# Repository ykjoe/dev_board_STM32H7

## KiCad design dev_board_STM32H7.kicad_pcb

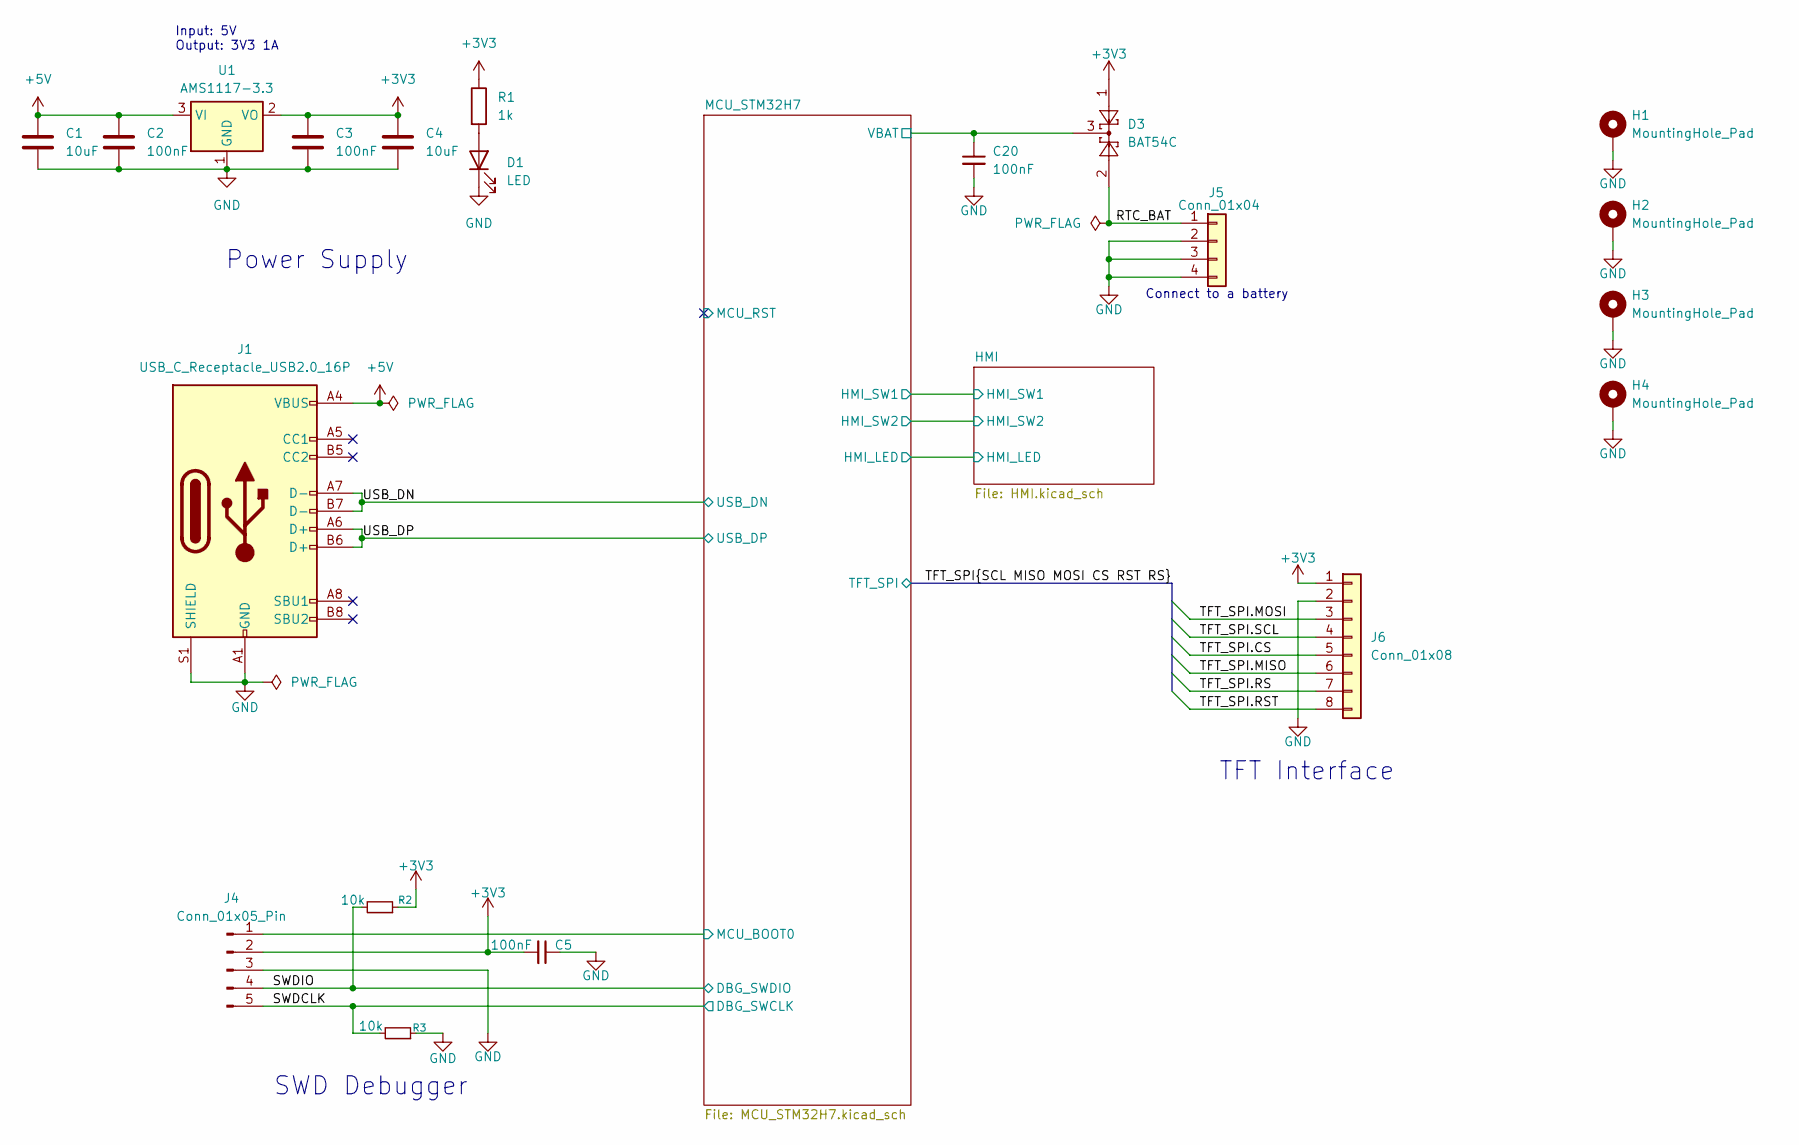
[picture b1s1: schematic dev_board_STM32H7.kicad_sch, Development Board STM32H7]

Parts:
C1, C4: 10uF; C_0805_2012Metric
C2, C3, C5, C20: 100nF; C_0402_1005Metric
D1: LED; LED_0603_1608Metric
D3: BAT54C; SOT-23
H1, H2, H3, H4: MountingHole_Pad; MountingHole_3mm_Pad
J1: USB_C_Receptacle_USB2.0_16P; USB-C-SMD_TYPE-C-16P-1
J4: Conn_01x05_Pin; PinHeader_1x05_P2.54mm_Vertical
J5: Conn_01x04; CONN-SMD_532610271
J6: Conn_01x08; PinHeader_1x08_P2.54mm_Vertical
R1: 1k; R_0402_1005Metric
R2, R3: 10k; R_0402_1005Metric
U1: AMS1117-3.3; SOT-223-3_TabPin2

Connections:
+3V3: C3.1, C4.1, C5.2, D3.1, J4.2, J6.1, R1.1, R2.1, U1.2 (VO); also elsewhere on the board
+5V: C1.1, C2.1, J1.A4 (VBUS), J1.A9 (VBUS), J1.B4 (VBUS), J1.B9 (VBUS), U1.3 (VI); also elsewhere on the board
/MCU_STM32H7/MCU_BOOT0: J4.1; also elsewhere on the board
/MCU_STM32H7/VBAT: C20.1, D3.3; also elsewhere on the board
/RTC_BAT: D3.2, J5.1
/SWDCLK: J4.5, R3.2; also elsewhere on the board
/SWDIO: J4.4, R2.2; also elsewhere on the board
/TFT_SPI.CS: J6.5; also elsewhere on the board
/TFT_SPI.MISO: J6.6; also elsewhere on the board
/TFT_SPI.MOSI: J6.3; also elsewhere on the board
/TFT_SPI.RS: J6.7; also elsewhere on the board
/TFT_SPI.RST: J6.8; also elsewhere on the board
/TFT_SPI.SCL: J6.4; also elsewhere on the board
/USB_DN: J1.A7 (D-), J1.B7 (D-); also elsewhere on the board
/USB_DP: J1.A6 (D+), J1.B6 (D+); also elsewhere on the board
GND: C1.2, C2.2, C3.2, C4.2, C5.1, C20.2, D1.1 (K), H1.1, H2.1, H3.1, H4.1, J1.A1 (GND), J1.A12 (GND), J1.B1 (GND), J1.B12 (GND), J1.S1 (SHIELD), J4.3, J5.2, J5.3, J5.4, J6.2, R3.1, U1.1 (GND); also elsewhere on the board
unnamed: D1.2 (A), R1.2

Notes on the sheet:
SWD Debugger
Connect to a battery
Power Supply
TFT Interface
Input: 5V Output: 3V3 1A

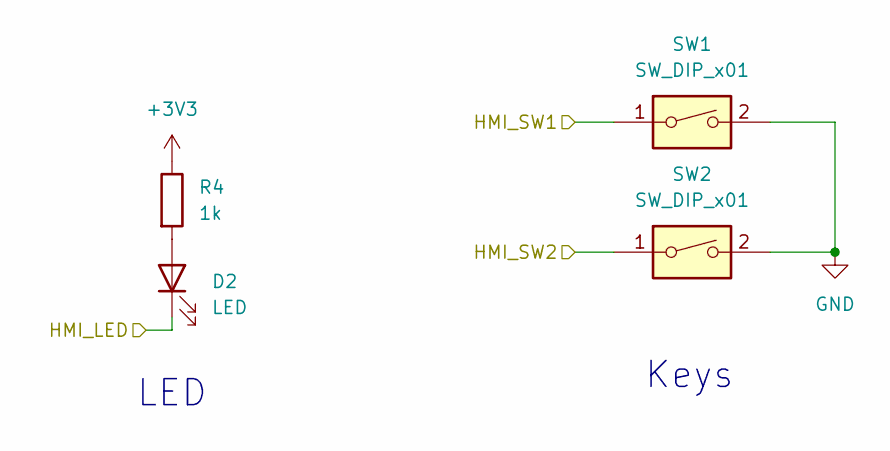
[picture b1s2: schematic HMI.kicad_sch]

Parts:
D2: LED; LED_0603_1608Metric
R4: 1k; R_0402_1005Metric
SW1, SW2: SW_DIP_x01; SW_DIP_SPSTx01_Slide_Copal_CHS-01A_W5.08mm_P1.27mm_JPin

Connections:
+3V3: R4.1; also elsewhere on the board
/MCU_STM32H7/PA1: D2.1 (K); also elsewhere on the board
/MCU_STM32H7/PC5: SW2.1; also elsewhere on the board
/MCU_STM32H7/PE3: SW1.1; also elsewhere on the board
GND: SW1.2, SW2.2; also elsewhere on the board
unnamed: D2.2 (A), R4.2

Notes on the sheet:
Keys
LED

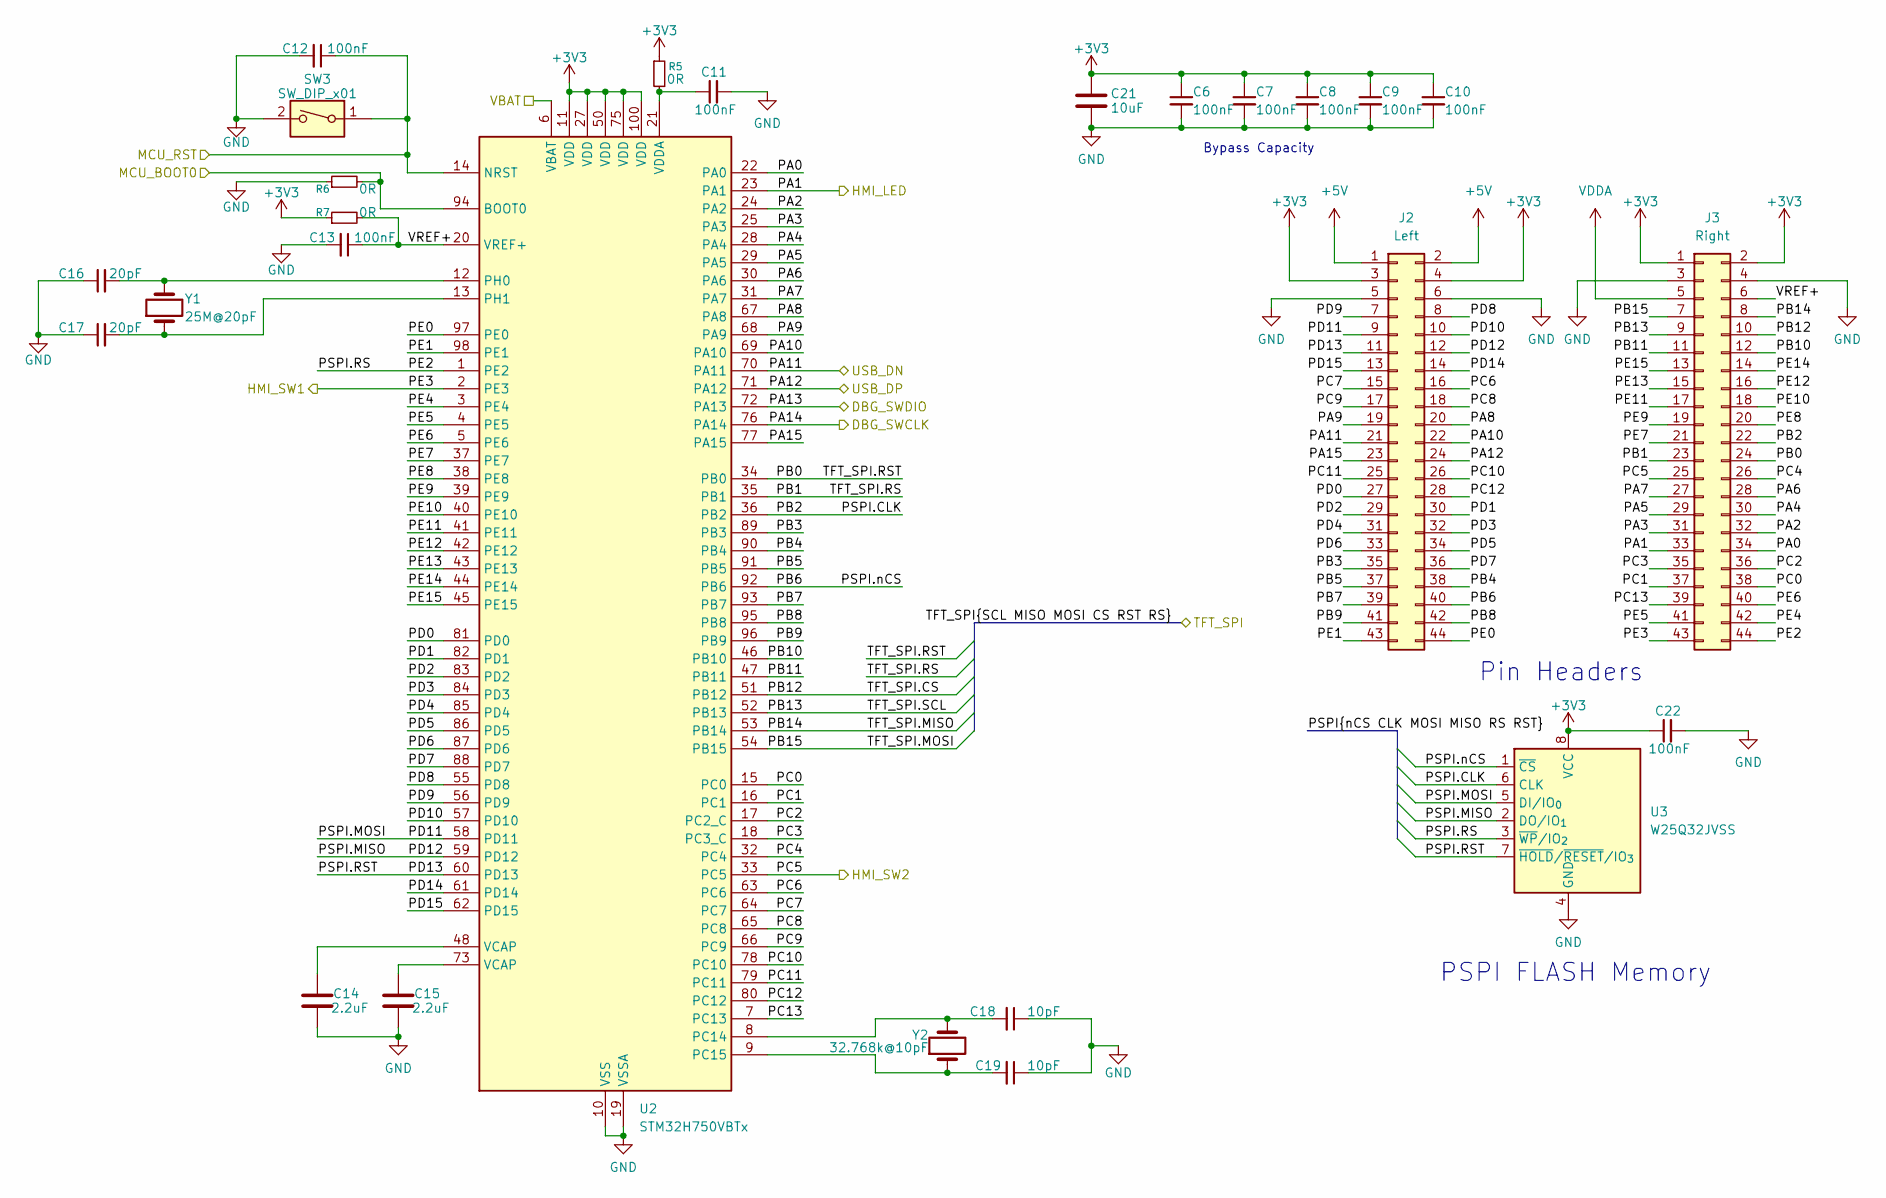
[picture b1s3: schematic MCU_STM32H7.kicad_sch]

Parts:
C6, C7, C8, C9, C10, C11, C12, C13, C22: 100nF; C_0402_1005Metric
C14, C15: 2.2uF; C_0603_1608Metric
C16, C17: 20pF; C_0402_1005Metric
C18, C19: 10pF; C_0402_1005Metric
C21: 10uF; C_0805_2012Metric
J2: Left; PinHeader_2x22_P2.54mm_Vertical
J3: Right; PinHeader_2x22_P2.54mm_Vertical
R5, R6, R7: 0R; R_0402_1005Metric
SW3: SW_DIP_x01; SW_DIP_SPSTx01_Slide_Copal_CHS-01A_W5.08mm_P1.27mm_JPin
U2: STM32H750VBTx; LQFP-100_14x14mm_P0.5mm
U3: W25Q32JVSS; SOIC-8_5.3x5.3mm_P1.27mm
Y1: 25M@20pF; Crystal_SMD_5032-2Pin_5.0x3.2mm
Y2: 32.768k@10pF; Crystal_SMD_3215-2Pin_3.2x1.5mm

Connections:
+3V3: C6.1, C7.1, C8.1, C9.1, C10.1, C21.1, C22.1, J2.3, J2.4, J3.1, J3.2, R5.1, R7.1, U2.11 (VDD), U2.27 (VDD), U2.50 (VDD), U2.75 (VDD), U2.100 (VDD), U3.8 (VCC); also elsewhere on the board
+5V: J2.1, J2.2; also elsewhere on the board
/MCU_STM32H7/MCU_BOOT0: R6.2, U2.94 (BOOT0); also elsewhere on the board
/MCU_STM32H7/MCU_RST: C12.1, SW3.1, U2.14 (NRST)
/MCU_STM32H7/PA0: J3.34, U2.22 (PA0)
/MCU_STM32H7/PA1: J3.33, U2.23 (PA1); also elsewhere on the board
/MCU_STM32H7/PA2: J3.32, U2.24 (PA2)
/MCU_STM32H7/PA3: J3.31, U2.25 (PA3)
/MCU_STM32H7/PA4: J3.30, U2.28 (PA4)
/MCU_STM32H7/PA5: J3.29, U2.29 (PA5)
/MCU_STM32H7/PA6: J3.28, U2.30 (PA6)
/MCU_STM32H7/PA7: J3.27, U2.31 (PA7)
/MCU_STM32H7/PA8: J2.20, U2.67 (PA8)
/MCU_STM32H7/PA9: J2.19, U2.68 (PA9)
/MCU_STM32H7/PA10: J2.22, U2.69 (PA10)
/MCU_STM32H7/PA15: J2.23, U2.77 (PA15)
/MCU_STM32H7/PB3: J2.35, U2.89 (PB3)
/MCU_STM32H7/PB4: J2.38, U2.90 (PB4)
/MCU_STM32H7/PB5: J2.37, U2.91 (PB5)
/MCU_STM32H7/PB7: J2.39, U2.93 (PB7)
/MCU_STM32H7/PB8: J2.42, U2.95 (PB8)
/MCU_STM32H7/PB9: J2.41, U2.96 (PB9)
/MCU_STM32H7/PB10: J3.12, U2.46 (PB10)
/MCU_STM32H7/PB11: J3.11, U2.47 (PB11)
/MCU_STM32H7/PC0: J3.38, U2.15 (PC0)
/MCU_STM32H7/PC1: J3.37, U2.16 (PC1)
/MCU_STM32H7/PC2: J3.36, U2.17 (PC2_C)
/MCU_STM32H7/PC3: J3.35, U2.18 (PC3_C)
/MCU_STM32H7/PC4: J3.26, U2.32 (PC4)
/MCU_STM32H7/PC5: J3.25, U2.33 (PC5); also elsewhere on the board
/MCU_STM32H7/PC6: J2.16, U2.63 (PC6)
/MCU_STM32H7/PC7: J2.15, U2.64 (PC7)
/MCU_STM32H7/PC8: J2.18, U2.65 (PC8)
/MCU_STM32H7/PC9: J2.17, U2.66 (PC9)
/MCU_STM32H7/PC10: J2.26, U2.78 (PC10)
/MCU_STM32H7/PC11: J2.25, U2.79 (PC11)
/MCU_STM32H7/PC12: J2.28, U2.80 (PC12)
/MCU_STM32H7/PC13: J3.39, U2.7 (PC13)
/MCU_STM32H7/PD0: J2.27, U2.81 (PD0)
/MCU_STM32H7/PD1: J2.30, U2.82 (PD1)
/MCU_STM32H7/PD2: J2.29, U2.83 (PD2)
/MCU_STM32H7/PD3: J2.32, U2.84 (PD3)
/MCU_STM32H7/PD4: J2.31, U2.85 (PD4)
/MCU_STM32H7/PD5: J2.34, U2.86 (PD5)
/MCU_STM32H7/PD6: J2.33, U2.87 (PD6)
/MCU_STM32H7/PD7: J2.36, U2.88 (PD7)
/MCU_STM32H7/PD8: J2.8, U2.55 (PD8)
/MCU_STM32H7/PD9: J2.7, U2.56 (PD9)
/MCU_STM32H7/PD10: J2.10, U2.57 (PD10)
/MCU_STM32H7/PD14: J2.14, U2.61 (PD14)
/MCU_STM32H7/PD15: J2.13, U2.62 (PD15)
/MCU_STM32H7/PE0: J2.44, U2.97 (PE0)
/MCU_STM32H7/PE1: J2.43, U2.98 (PE1)
/MCU_STM32H7/PE3: J3.43, U2.2 (PE3); also elsewhere on the board
/MCU_STM32H7/PE4: J3.42, U2.3 (PE4)
/MCU_STM32H7/PE5: J3.41, U2.4 (PE5)
/MCU_STM32H7/PE6: J3.40, U2.5 (PE6)
/MCU_STM32H7/PE7: J3.21, U2.37 (PE7)
/MCU_STM32H7/PE8: J3.20, U2.38 (PE8)
/MCU_STM32H7/PE9: J3.19, U2.39 (PE9)
/MCU_STM32H7/PE10: J3.18, U2.40 (PE10)
/MCU_STM32H7/PE11: J3.17, U2.41 (PE11)
/MCU_STM32H7/PE12: J3.16, U2.42 (PE12)
/MCU_STM32H7/PE13: J3.15, U2.43 (PE13)
/MCU_STM32H7/PE14: J3.14, U2.44 (PE14)
/MCU_STM32H7/PE15: J3.13, U2.45 (PE15)
/MCU_STM32H7/PSPI.CLK: J3.22, U2.36 (PB2), U3.6 (CLK)
/MCU_STM32H7/PSPI.MISO: J2.12, U2.59 (PD12), U3.2 (DO/IO_{1})
/MCU_STM32H7/PSPI.MOSI: J2.9, U2.58 (PD11), U3.5 (DI/IO_{0})
/MCU_STM32H7/PSPI.RS: J3.44, U2.1 (PE2), U3.3 (~WP/IO_{2})
/MCU_STM32H7/PSPI.RST: J2.11, U2.60 (PD13), U3.7 (~HOLD/~RESET/IO_{3})
/MCU_STM32H7/PSPI.nCS: J2.40, U2.92 (PB6), U3.1 (~CS)
/MCU_STM32H7/VBAT: U2.6 (VBAT); also elsewhere on the board
/MCU_STM32H7/VREF+: C13.1, J3.6, R7.2, U2.20 (VREF+)
/SWDCLK: U2.76 (PA14); also elsewhere on the board
/SWDIO: U2.72 (PA13); also elsewhere on the board
/TFT_SPI.CS: J3.10, U2.51 (PB12); also elsewhere on the board
/TFT_SPI.MISO: J3.8, U2.53 (PB14); also elsewhere on the board
/TFT_SPI.MOSI: J3.7, U2.54 (PB15); also elsewhere on the board
/TFT_SPI.RS: J3.23, U2.35 (PB1); also elsewhere on the board
/TFT_SPI.RST: J3.24, U2.34 (PB0); also elsewhere on the board
/TFT_SPI.SCL: J3.9, U2.52 (PB13); also elsewhere on the board
/USB_DN: J2.21, U2.70 (PA11); also elsewhere on the board
/USB_DP: J2.24, U2.71 (PA12); also elsewhere on the board
GND: C6.2, C7.2, C8.2, C9.2, C10.2, C11.2, C12.2, C13.2, C14.1, C15.1, C16.1, C17.1, C18.1, C19.1, C21.2, C22.2, J2.5, J2.6, J3.3, J3.4, R6.1, SW3.2, U2.10 (VSS), U2.19 (VSSA), U2.26 (VSS), U2.49 (VSS), U2.74 (VSS), U2.99 (VSS), U3.4 (GND); also elsewhere on the board
unnamed: C14.2, U2.48 (VCAP)
unnamed: C15.2, U2.73 (VCAP)
unnamed: C18.2, U2.8 (PC14), Y2.2
unnamed: C19.2, U2.9 (PC15), Y2.1
unnamed: C16.2, U2.12 (PH0), Y1.2
unnamed: C17.2, U2.13 (PH1), Y1.1
unnamed: C11.1, R5.2, U2.21 (VDDA)
VDDA: J3.5

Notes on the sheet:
Bypass Capacity
PSPI FLASH Memory
Pin Headers

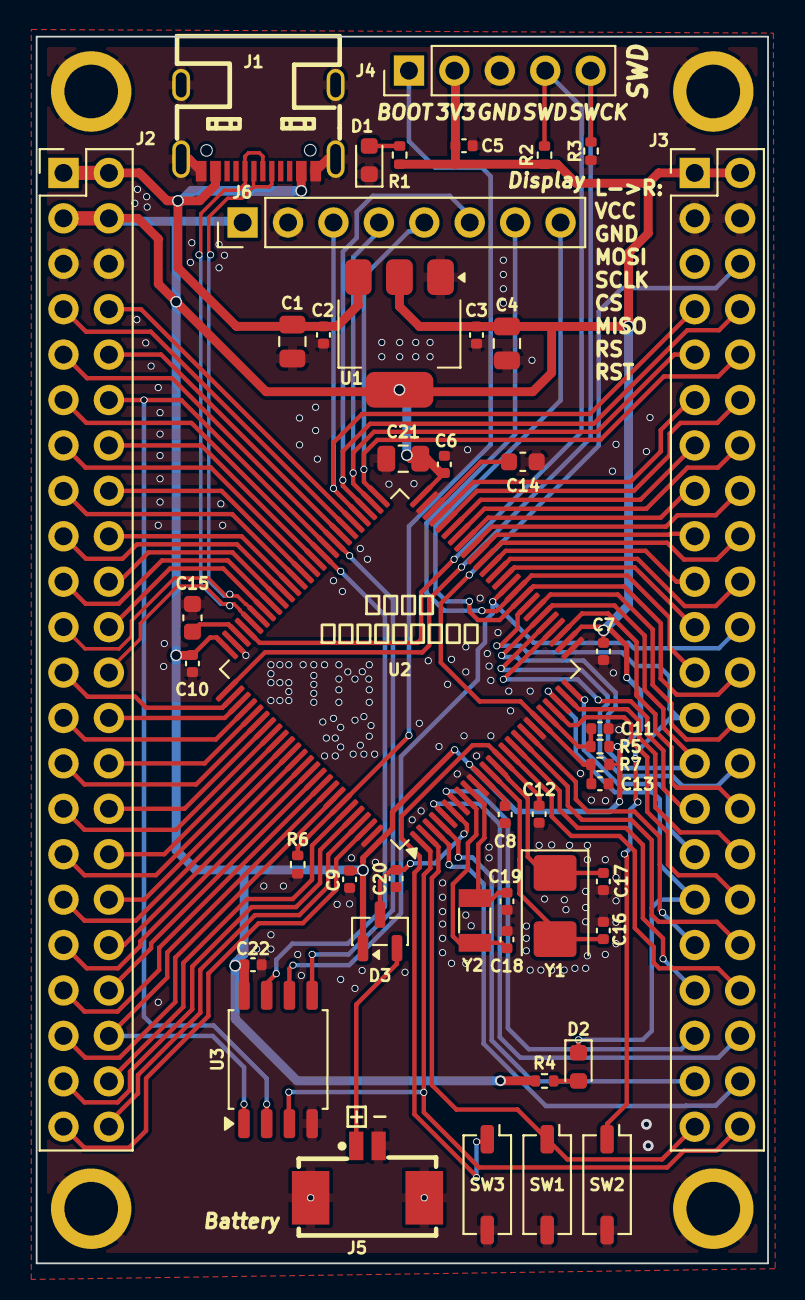
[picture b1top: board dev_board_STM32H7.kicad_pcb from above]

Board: 2 copper layers, 40.9 x 68.6 mm, 50 parts (0 on the bottom side), 95 nets.

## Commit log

2025-10-18 Finish Circuit Design for STM32 Devment Board
2025-10-18 Add Some Comments
2026-01-09 Modify line width of power strack
2026-01-12 Generate output files
